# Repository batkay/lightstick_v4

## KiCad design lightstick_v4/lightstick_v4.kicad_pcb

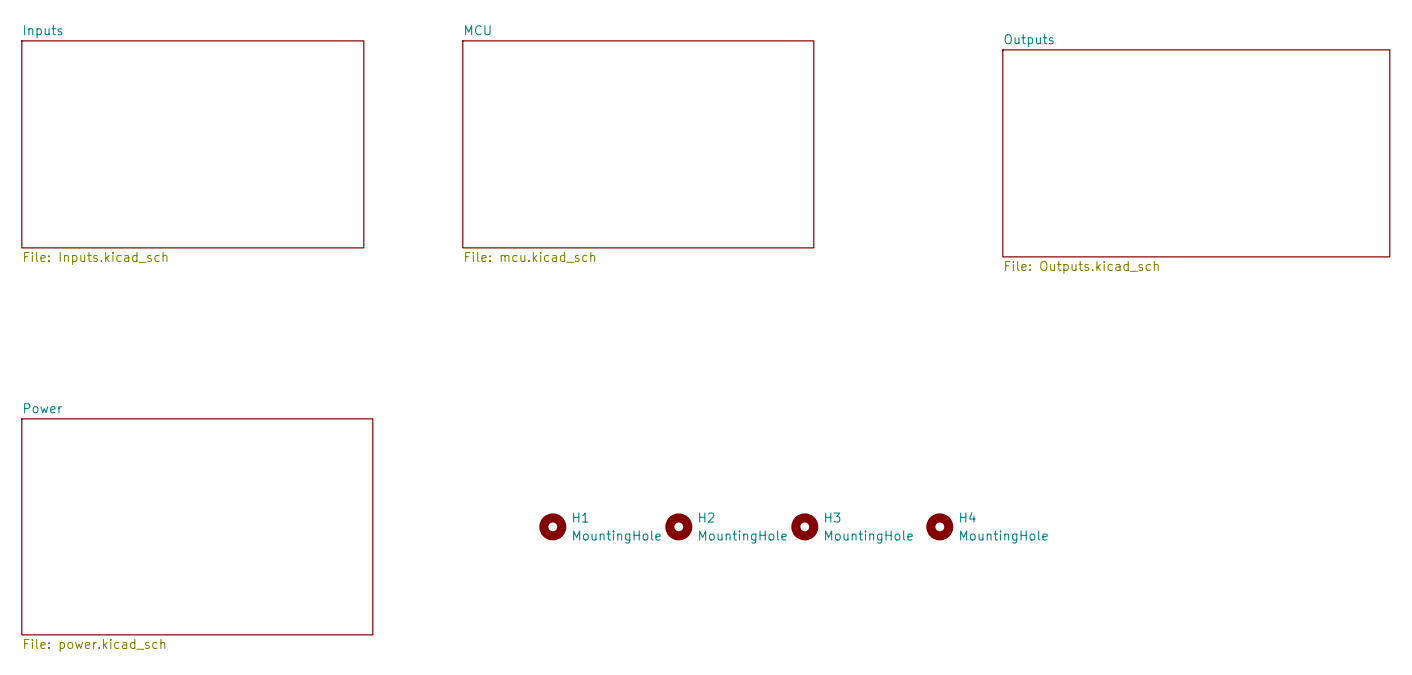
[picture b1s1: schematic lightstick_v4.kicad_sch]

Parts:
H1, H2, H3, H4: MountingHole; MountingHole_2.1mm

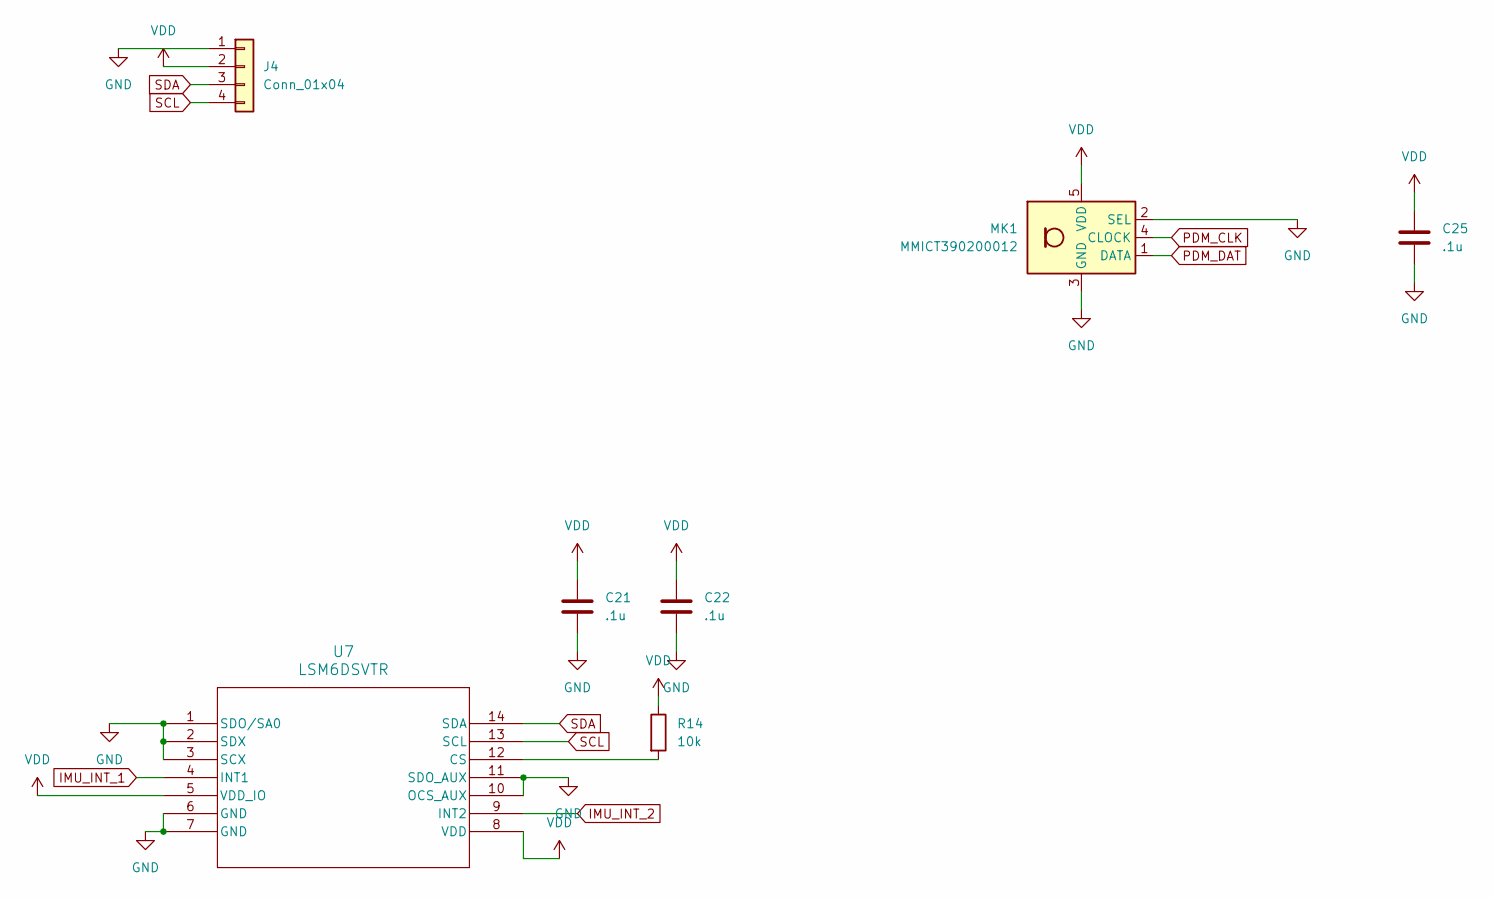
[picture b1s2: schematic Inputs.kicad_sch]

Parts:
C21, C22, C25: .1u; C_0402_1005Metric; MPN C77020; LCSC PN C77020
J4: Conn_01x04; JST_SH_BM04B-SRSS-TB_1x04-1MP_P1.00mm_Vertical; Part Number JST BM04B-SRSS-TB(LF)(SN); LCSC PN C495539
MK1: MMICT390200012; Knowles_LGA-5_3.5x2.65mm; Part Number MMICT390200012; LCSC PN C3171752
R14: 10k; R_0603_1608Metric; MPN C98220; LCSC PN C98220
U7: LSM6DSVTR; LGA14-L_2P59X3P1X0P5_STM; MPN C17496470; LCSC PN C17496470

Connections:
GND: C21.2, C22.2, C25.2, J4.1, MK1.2 (SEL), MK1.3 (GND), U7.1 (SDO/SA0), U7.2 (SDX), U7.3 (SCX), U7.6 (GND), U7.7 (GND), U7.10 (OCS_AUX), U7.11 (SDO_AUX); also elsewhere on the board
IMU_INT_1: U7.4 (INT1); also elsewhere on the board
IMU_INT_2: U7.9 (INT2); also elsewhere on the board
unnamed: R14.2, U7.12 (CS)
PDM_CLK: MK1.4 (CLOCK); also elsewhere on the board
PDM_DAT: MK1.1 (DATA); also elsewhere on the board
SCL: J4.4, U7.13 (SCL); also elsewhere on the board
SDA: J4.3, U7.14 (SDA); also elsewhere on the board
VDD: C21.1, C22.1, C25.1, J4.2, MK1.5 (VDD), R14.1, U7.5 (VDD_IO), U7.8 (VDD); also elsewhere on the board

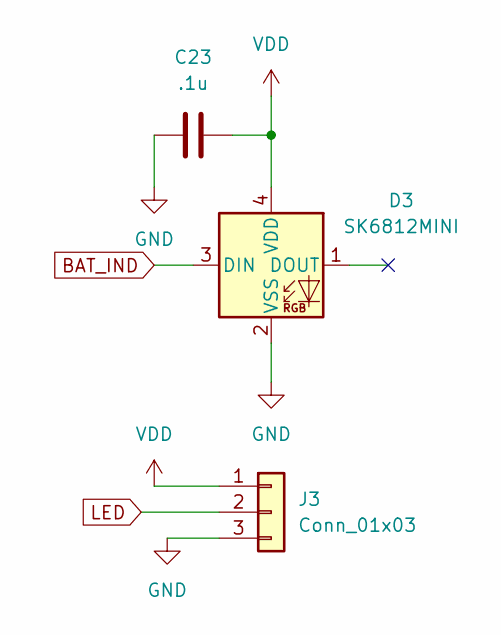
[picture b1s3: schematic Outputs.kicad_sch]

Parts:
C23: .1u; C_0402_1005Metric; MPN C77020; LCSC PN C77020
D3: SK6812MINI; LED_SK6812MINI_PLCC4_3.5x3.5mm_P1.75mm; MPN C7423117; LCSC PN C7423117
J3: Conn_01x03; PinHeader_1x03_P2.54mm_Horizontal; MPN C92159; LCSC PN C92159

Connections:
BAT_IND: D3.3 (DIN); also elsewhere on the board
GND: C23.1, D3.2 (VSS), J3.3; also elsewhere on the board
LED: J3.2; also elsewhere on the board
VDD: C23.2, D3.4 (VDD), J3.1; also elsewhere on the board

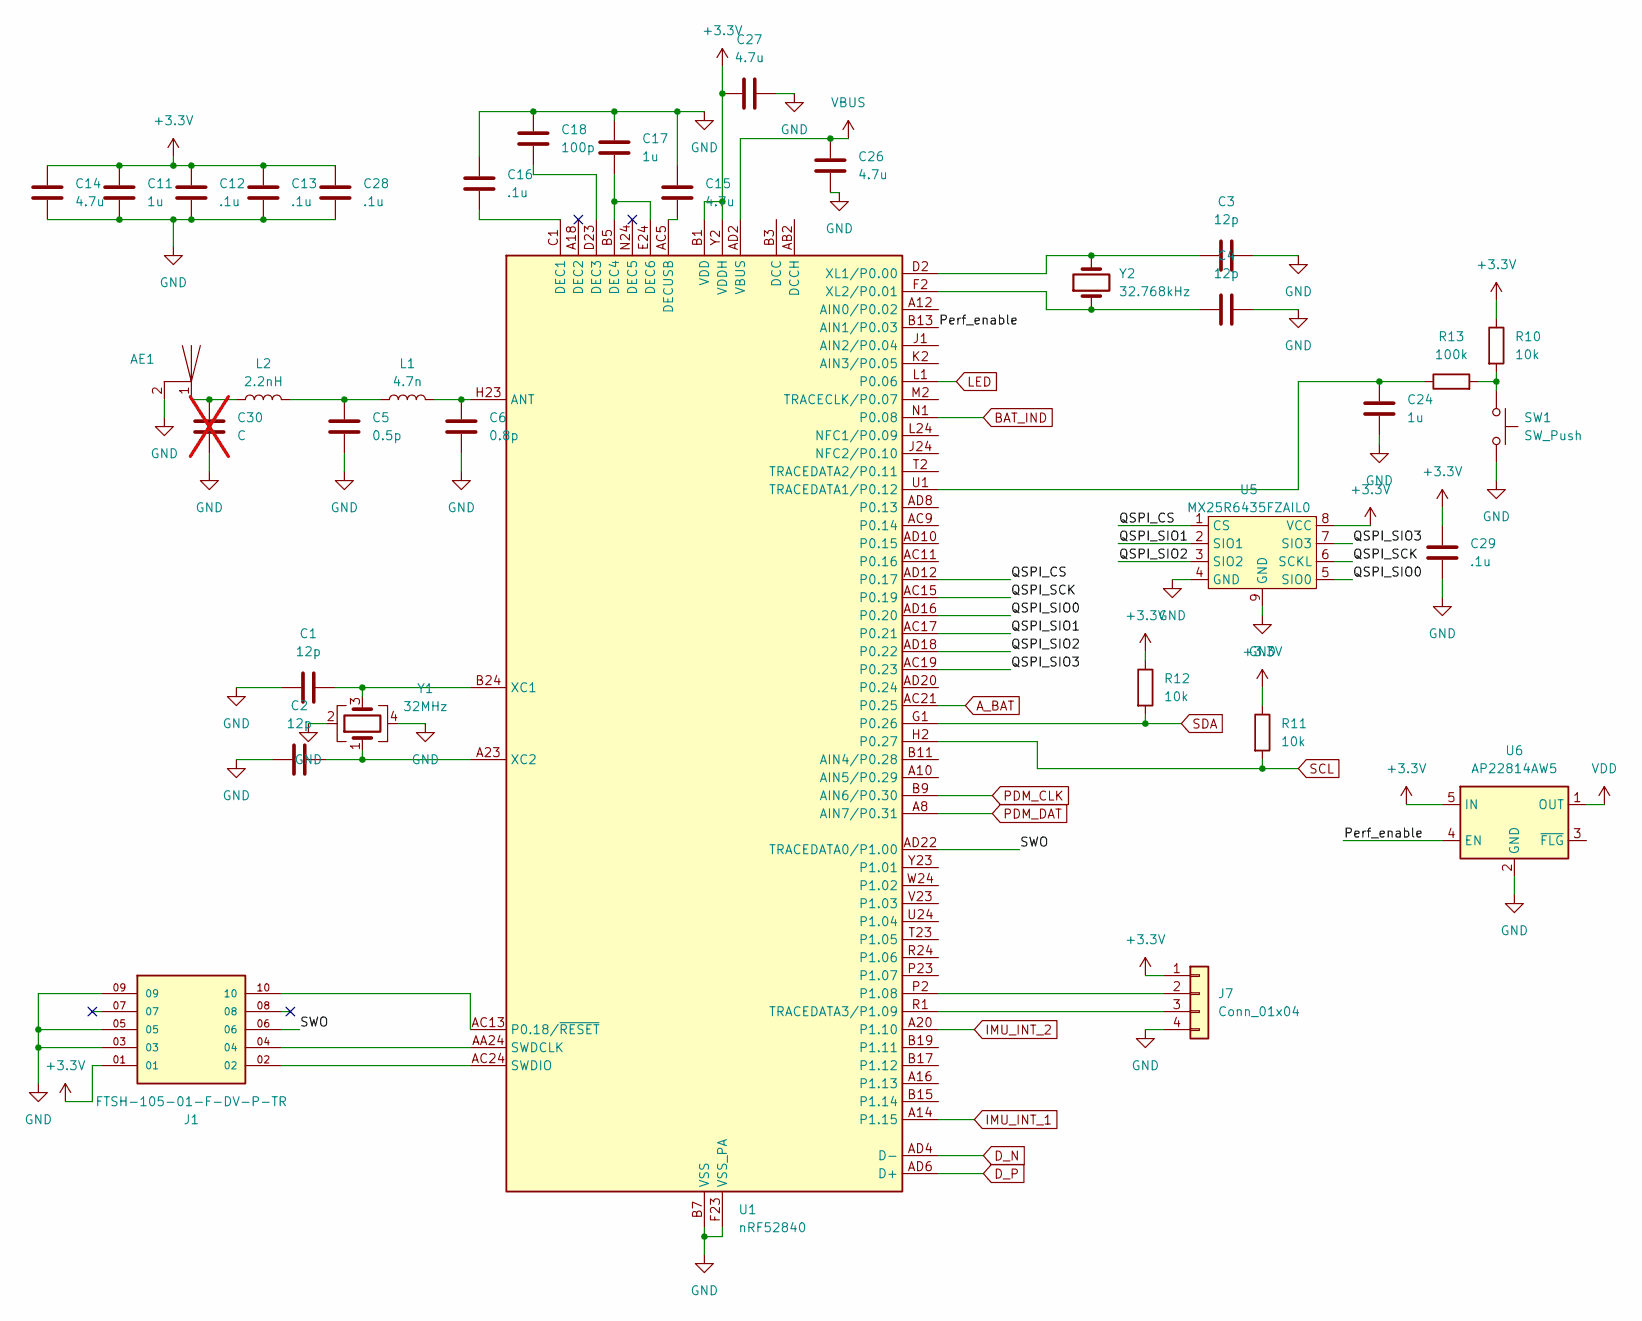
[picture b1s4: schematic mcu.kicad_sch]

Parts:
AE1: Trace Antenna
C1, C2, C3, C4: 12p; C_0402_1005Metric; MPN C76948; LCSC PN C76948
C5: 0.5p; C_0402_1005Metric; MPN C76912; LCSC PN C76912
C6: 0.8p; C_0402_1005Metric; MPN C88902; LCSC PN C88902
C11, C17, C24: 1u; C_0603_1608Metric; MPN C85862; LCSC PN C85862
C12, C13, C16, C28, C29: .1u; C_0402_1005Metric; MPN C77020; LCSC PN C77020
C14, C15, C26, C27: 4.7u; C_0603_1608Metric; MPN C19666; LCSC PN C19666
C18: 100p; C_0402_1005Metric; MPN C26409; LCSC PN C26409
C30: C; C_0402_1005Metric; not fitted
J1: FTSH-105-01-F-DV-P-TR; SAMTEC_FTSH-105-01-F-DV-P-TR; PARTREV R; LCSC PN C2932107
J7: Conn_01x04; PinHeader_1x04_P2.54mm_Vertical; MPN C52016392; LCSC PN C52016392
L1: 4.7n; L_0402_1005Metric; MPN C412337; LCSC PN C412337
L2: 2.2nH; C_0402_1005Metric; MPN C162540; LCSC PN C162540
R10, R11, R12: 10k; R_0603_1608Metric; MPN C98220; LCSC PN C98220
R13: 100k; R_0603_1608Metric; MPN C14675; LCSC PN C14675
SW1: SW_Push; Hotswap_Kailh_MX_Top; MPN C41430893; LCSC PN C41430893
U1: nRF52840; Nordic_AQFN-73-1EP_7x7mm_P0.5mm; Part Number NRF52840-QIAA-R; LCSC PN C190794
U5: MX25R6435FZAIL0; WSON-8-1EP_4x4mm_P0.8mm_EP1.98x3mm; Part Number MX25R6435FZAIL0; LCSC PN C2802847
U6: AP22814AW5; SOT-23-5; MPN C2680321; LCSC PN C2680321
Y1: 32MHz; Crystal_SMD_2016-4Pin_2.0x1.6mm; Part Number Murata XRCGB32M000F2P10R0; LCSC PN C341819
Y2: 32.768kHz; Crystal_SMD_3215-2Pin_3.2x1.5mm; Part Number Seiko SC-32S32.768kHz20PPM9pF; LCSC PN C97605

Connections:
+3.3V: C11.1, C12.1, C13.1, C14.1, C27.1, C28.1, C29.1, J1.01, J7.1, R10.1, R11.1, R12.1, U1.A22 (VDD), U1.AD14 (VDD), U1.AD23 (VDD), U1.B1 (VDD), U1.W1 (VDD), U1.Y2 (VDDH), U5.8 (VCC), U6.5 (IN); also elsewhere on the board
/MCU/Perf_enable: U1.B13 (AIN1/P0.03), U6.4 (EN)
/MCU/QSPI_CS: U1.AD12 (P0.17), U5.1 (CS)
/MCU/QSPI_SCK: U1.AC15 (P0.19), U5.6 (SCKL)
/MCU/QSPI_SIO0: U1.AD16 (P0.20), U5.5 (SIO0)
/MCU/QSPI_SIO1: U1.AC17 (P0.21), U5.2 (SIO1)
/MCU/QSPI_SIO2: U1.AD18 (P0.22), U5.3 (SIO2)
/MCU/QSPI_SIO3: U1.AC19 (P0.23), U5.7 (SIO3)
/MCU/SWO: J1.06, U1.AD22 (TRACEDATA0/P1.00)
A_BAT: U1.AC21 (P0.25); also elsewhere on the board
BAT_IND: U1.N1 (P0.08); also elsewhere on the board
D_N: U1.AD4 (D-); also elsewhere on the board
D_P: U1.AD6 (D+); also elsewhere on the board
GND: AE1.2, C1.1, C2.1, C3.2, C4.2, C5.2, C6.2, C11.2, C12.2, C13.2, C14.2, C15.2, C16.1, C17.1, C18.1, C24.2, C26.2, C27.2, C28.2, C29.2, C30.2, J1.03, J1.05, J1.09, J7.4, SW1.2, U1.B7 (VSS), U1.EP (VSS), U1.F23 (VSS_PA), U5.4 (GND), U5.9 (GND), U6.2 (GND), Y1.2, Y1.4; also elsewhere on the board
IMU_INT_1: U1.A14 (P1.15); also elsewhere on the board
IMU_INT_2: U1.A20 (P1.10); also elsewhere on the board
LED: U1.L1 (P0.06); also elsewhere on the board
unnamed: AE1.1, C30.1, L2.1
unnamed: C5.1, L1.1, L2.2
unnamed: J7.2, U1.P2 (P1.08)
unnamed: J7.3, U1.R1 (TRACEDATA3/P1.09)
unnamed: R10.2, R13.2, SW1.1
unnamed: C6.1, L1.2, U1.H23 (ANT)
unnamed: C16.2, U1.C1 (DEC1)
unnamed: C18.2, U1.D23 (DEC3)
unnamed: C17.2, U1.B5 (DEC4), U1.E24 (DEC6)
unnamed: C15.1, U1.AC5 (DECUSB)
unnamed: J1.10, U1.AC13 (P0.18/~RESET)
unnamed: J1.04, U1.AA24 (SWDCLK)
unnamed: J1.02, U1.AC24 (SWDIO)
unnamed: C24.1, R13.1, U1.U1 (TRACEDATA1/P0.12)
unnamed: C1.2, U1.B24 (XC1), Y1.3
unnamed: C2.2, U1.A23 (XC2), Y1.1
unnamed: C3.1, U1.D2 (XL1/P0.00), Y2.2
unnamed: C4.1, U1.F2 (XL2/P0.01), Y2.1
PDM_CLK: U1.B9 (AIN6/P0.30); also elsewhere on the board
PDM_DAT: U1.A8 (AIN7/P0.31); also elsewhere on the board
SCL: R11.2, U1.H2 (P0.27); also elsewhere on the board
SDA: R12.2, U1.G1 (P0.26); also elsewhere on the board
VBUS: C26.1, U1.AD2 (VBUS); also elsewhere on the board
VDD: U6.1 (OUT); also elsewhere on the board

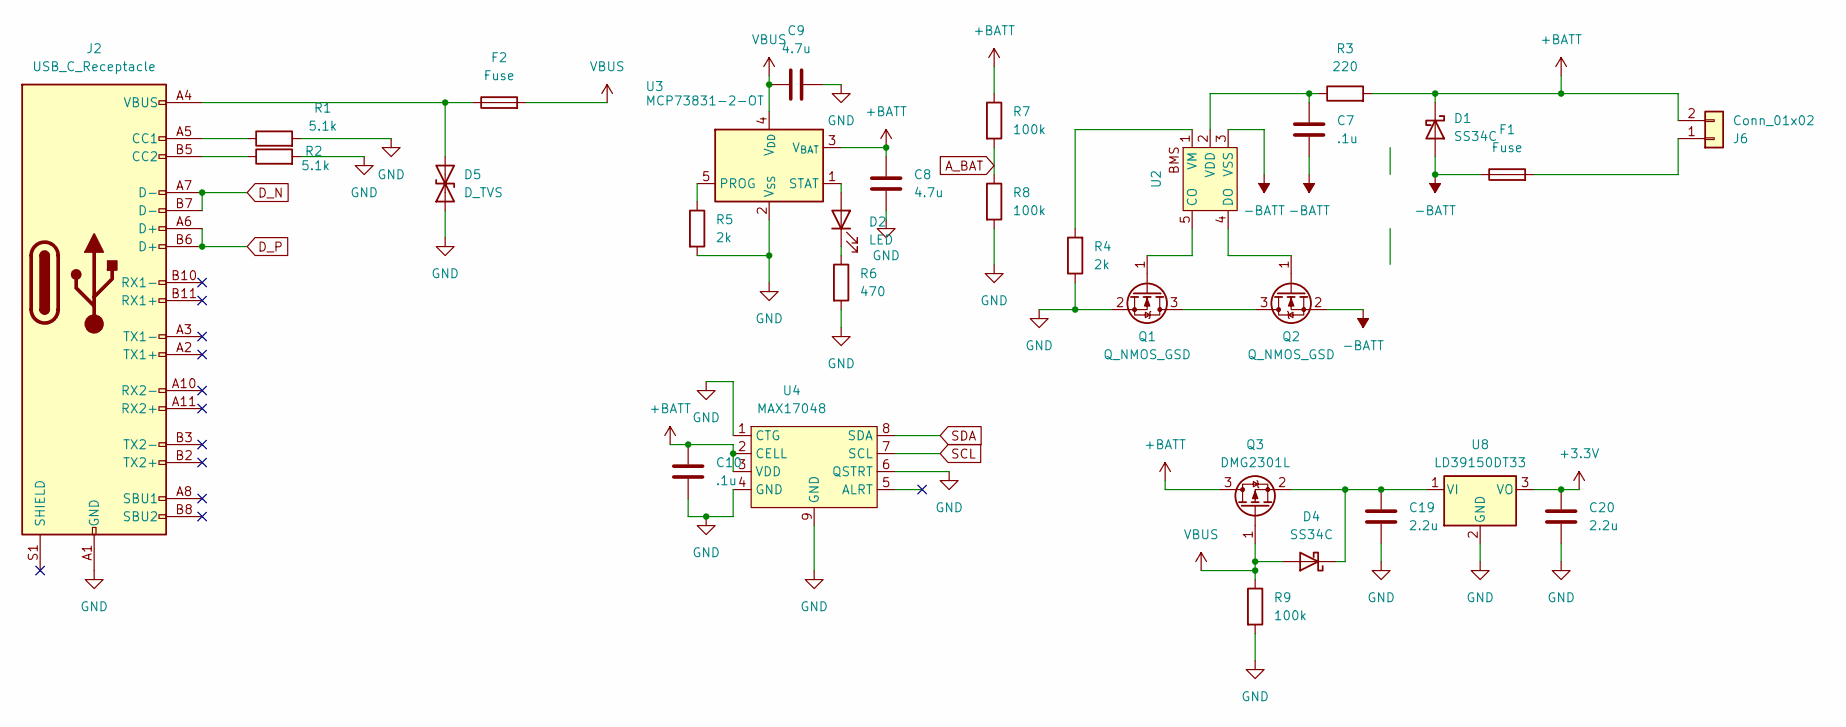
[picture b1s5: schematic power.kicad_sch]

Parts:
C7, C10: .1u; C_0402_1005Metric; MPN C77020; LCSC PN C77020
C8, C9: 4.7u; C_0603_1608Metric; MPN C19666; LCSC PN C19666
C19, C20: 2.2u; C_0603_1608Metric; MPN C415535; LCSC PN C415535
D1, D4: SS34C; D_SMC; MPN C13763; LCSC PN C13763
D2: LED; LED_0805_2012Metric; MPN C2293; LCSC PN C2293
D5: D_TVS; D_0402_1005Metric; Part Number TPD1E10B06DPYR; LCSC PN C48260
F1: Fuse; Fuse_1210_3225Metric; Part Number Shenzhen JDT Fuse ASMD1210-075; LCSC PN C20806
F2: Fuse; Fuse_1210_3225Metric; Part Number TECHFUSE SL1210350; LCSC PN C20806
J2: USB_C_Receptacle; USB_C_Receptacle_GCT_USB4105-xx-A_16P_TopMnt_Horizontal; Part Number MC-107D; LCSC PN C2874568
J6: Conn_01x02; JST_PH_B2B-PH-K_1x02_P2.00mm_Vertical; MPN C131337; LCSC PN C131337
Q1, Q2: Q_NMOS_GSD; TSOT-23; Part Number DMG3414U-7; LCSC PN C260927
Q3: DMG2301L; SOT-23; MPN C102619; LCSC PN C102619
R1, R2: 5.1k; R_0603_1608Metric; MPN C122969; LCSC PN C122969
R3: 220; R_0603_1608Metric; MPN C107696; LCSC PN C107696
R4, R5: 2k; R_0603_1608Metric; MPN C105576; LCSC PN C105576
R6: 470; R_0603_1608Metric; MPN C114669; LCSC PN C114669
R7, R8: 100k; R_0603_1608Metric; MPN C19666; LCSC PN C14675
R9: 100k; R_0603_1608Metric; MPN C14675; LCSC PN C14675
U2: SOT-23-5; Part Number S-8211CAZ-M5T1G; LCSC PN C5881307
U3: MCP73831-2-OT; SOT-23-5; Part Number MCP73831T-2ACI/OT; LCSC PN C424093
U4: MAX17048; TDFN-8-1EP_2x2mm_P0.5mm_EP0.8x1.2mm; MPN C2682616; LCSC PN C2682616
U8: LD39150DT33; TO-252-3_TabPin2; MPN C155559; LCSC PN C155559

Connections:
+3.3V: C20.1, U8.3 (VO); also elsewhere on the board
+BATT: C8.1, C10.1, D1.1 (K), J6.2, Q3.3 (D), R3.2, R7.1, U3.3 (V_{BAT}), U4.2 (CELL), U4.3 (VDD)
-BATT: C7.2, D1.2 (A), F1.1, Q2.2 (S), U2.3 (VSS)
A_BAT: R7.2, R8.1; also elsewhere on the board
D_N: J2.A7 (D-), J2.B7 (D-); also elsewhere on the board
D_P: J2.A6 (D+), J2.B6 (D+); also elsewhere on the board
GND: C8.2, C9.2, C10.2, C19.2, C20.2, D5.1 (A1), J2.A1 (GND), J2.A12 (GND), J2.B1 (GND), J2.B12 (GND), Q1.2 (S), R1.2, R2.2, R4.1, R5.2, R6.2, R8.2, R9.2, U3.2 (V_{SS}), U4.1 (CTG), U4.4 (GND), U4.6 (QSTRT), U4.9 (GND), U8.2 (GND); also elsewhere on the board
unnamed: D2.2 (A), U3.1 (STAT)
unnamed: D2.1 (K), R6.1
unnamed: C19.1, D4.1 (K), Q3.2 (S), U8.1 (VI)
unnamed: D5.2 (A2), F2.1, J2.A4 (VBUS), J2.A9 (VBUS), J2.B4 (VBUS), J2.B9 (VBUS)
unnamed: J2.A5 (CC1), R1.1
unnamed: J2.B5 (CC2), R2.1
unnamed: F1.2, J6.1
unnamed: Q1.3 (D), Q2.3 (D)
unnamed: Q1.1 (G), U2.5 (CO)
unnamed: Q2.1 (G), U2.4 (DO)
unnamed: C7.1, R3.1, U2.2 (VDD)
unnamed: R4.2, U2.1 (VM)
unnamed: R5.1, U3.5 (PROG)
SCL: U4.7 (SCL); also elsewhere on the board
SDA: U4.8 (SDA); also elsewhere on the board
VBUS: C9.1, D4.2 (A), F2.2, Q3.1 (G), R9.1, U3.4 (V_{DD}); also elsewhere on the board

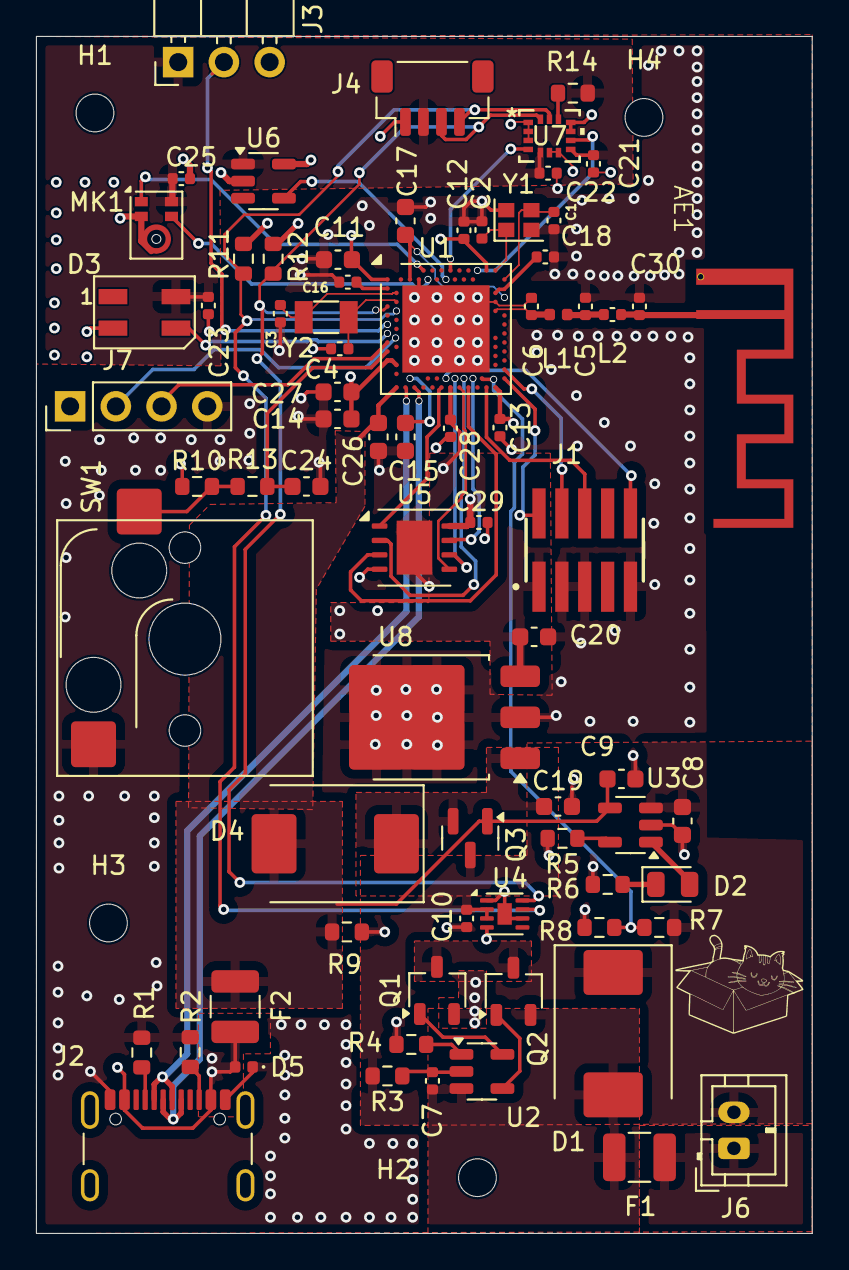
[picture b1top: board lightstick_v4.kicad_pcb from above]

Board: 4 copper layers, 43.1 x 66.5 mm, 79 parts (0 on the bottom side), 57 nets.

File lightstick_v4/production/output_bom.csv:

Designator,Footprint,Quantity,Value,LCSC Part #
"C1, C2, C3, C4",0402,4,12p,C76948
"C10, C12, C13, C16, C21, C22, C23, C25, C28, C29, C7",0402,11,.1u,C77020
"C11, C17, C24",0603,3,1u,C85862
"C14, C15, C26, C27, C8, C9",0603,6,4.7u,C19666
C18,0402,1,100p,C77177
"C19, C20",0603,2,2.2u,C415535
C5,0402,1,0.5p,C76912
C6,0402,1,0.8p,C88902
"D1, D4",D_SMC,2,SS34C,C13763
D2,0805,1,LED,C965817
D3,LED_SK6812MINI_PLCC4_3.5x3.5mm_P1.75mm,1,SK6812MINI,C7423117
D5,0402,1,D_TVS,C48260
"F1, F2",1210,2,Fuse,C20806
J1,SAMTEC_FTSH-105-01-F-DV-P-TR,1,FTSH-105-01-F-DV-P-TR,C2932107
J2,USB_C_Receptacle_GCT_USB4105-xx-A_16P_TopMnt_Horizontal,1,USB_C_Receptacle,C2874568
J3,PinHeader_1x03_P2.54mm_Horizontal,1,Conn_01x03,C92159
J4,JST_SH_BM04B-SRSS-TB_1x04-1MP_P1.00mm_Vertical,1,Conn_01x04,C495539
J6,JST_PH_B2B-PH-K_1x02_P2.00mm_Vertical,1,Conn_01x02,C131337
J7,PinHeader_1x04_P2.54mm_Vertical,1,Conn_01x04,C52016392
L1,0402,1,4.7n,C412337
L2,0402,1,2.2nH,C162540
MK1,Knowles_LGA-5_3.5x2.65mm,1,MMICT390200012,C3171752
"Q1, Q2",TSOT-23,2,Q_NMOS_GSD,C260927
Q3,SOT-23,1,DMG2301L,C102619
"R1, R2",0603,2,5.1k,C122969
"R10, R11, R12, R14",0603,4,10k,C98220
"R13, R7, R8, R9",0603,4,100k,C14675
R3,0603,1,220,C107696
"R4, R5",0603,2,2k,C105576
R6,0603,1,470,C114669
SW1,Hotswap_Kailh_MX_Top,1,SW_Push,C41430893
U1,Nordic_AQFN-73-1EP_7x7mm_P0.5mm,1,nRF52840,C190794
U2,SOT-23-5,1,~,C5881307
U3,SOT-23-5,1,MCP73831-2-OT,C424093
U4,TDFN-8-1EP_2x2mm_P0.5mm_EP0.8x1.2mm,1,MAX17048,C2682616
U5,WSON-8-1EP_4x4mm_P0.8mm_EP1.98x3mm,1,MX25R6435FZAIL0,C2802847
U6,SOT-23-5,1,AP22814AW5,C2680321
U7,LGA14-L_2P59X3P1X0P5_STM,1,LSM6DSVTR,C17496470
U8,TO-252-3_TabPin2,1,LD39150DT33,C155559
Y1,Crystal_SMD_2016-4Pin_2.0x1.6mm,1,32MHz,C341819
Y2,Crystal_SMD_3215-2Pin_3.2x1.5mm,1,32.768kHz,C97605

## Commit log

2025-12-28 Initial release
2026-01-29 rev1
